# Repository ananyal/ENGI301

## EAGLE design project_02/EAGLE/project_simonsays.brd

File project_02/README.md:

Simon Says PCB
This repository provides the files for the PCB implementation of the following Hackster Project: https://www.hackster.io/al85/simon-says-pattern-mini-game-16e997

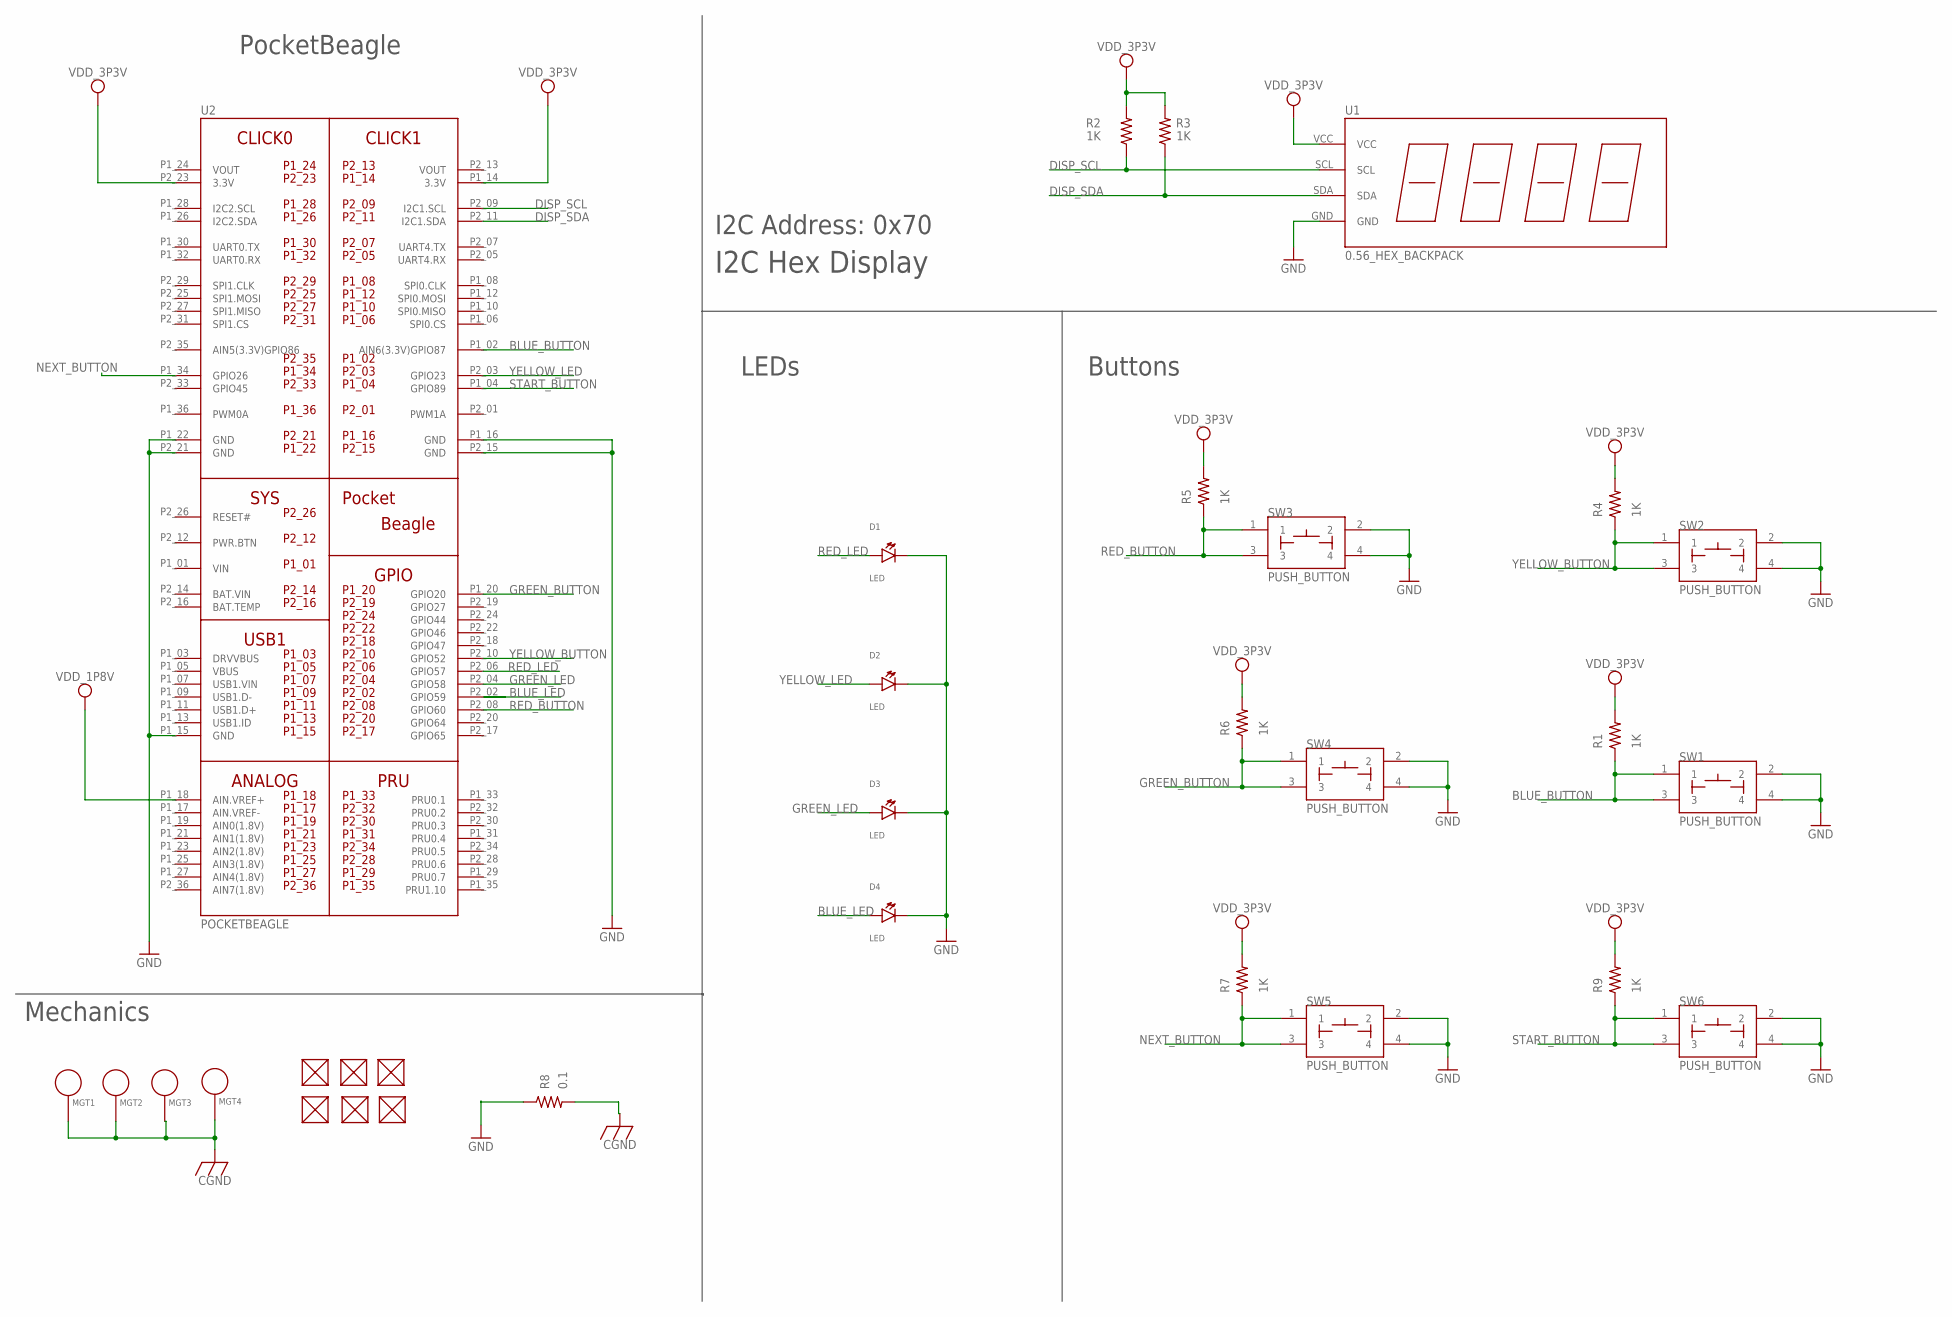
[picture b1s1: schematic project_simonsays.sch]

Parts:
D1, D2, D3, D4: LED; EIA-STD
FUD1, FUD2, FUD3, FUD4, FUD5, FUD6: FIDUCIAL; FIDUCIAL_40MIL
MGT1, MGT2, MGT3, MGT4: MOUNTING_HOLE
R1, R2, R3, R4, R5, R6, R7, R9: 1K; R0603
R8: 0.1; R0805
SW1, SW2, SW3, SW4, SW5, SW6: PUSH_BUTTON; BUTTON_12.5MM
U1: 0.56_HEX_BACKPACK
U2: POCKETBEAGLE

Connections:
BAT.VIN: U2.P2_14 (BAT.VIN)
BLUE_BUTTON: R1.1, SW1.1, SW1.3, U2.P1_02 (AIN6(3.3V)GPIO87)
BLUE_LED: D4.ANODE, U2.P2_02 (GPIO59)
CGND: MGT1.P$1, MGT2.P$1, MGT3.P$1, MGT4.P$1, R8.2
DISP_SCL: R2.1, U1.SCL, U2.P2_09 (I2C1.SCL)
DISP_SDA: R3.1, U1.SDA, U2.P2_11 (I2C1.SDA)
GND: D1.CATHODE, D2.CATHODE, D3.CATHODE, D4.CATHODE, R8.1, SW1.2, SW1.4, SW2.2, SW2.4, SW3.2, SW3.4, SW4.2, SW4.4, SW5.2, SW5.4, SW6.2, SW6.4, U1.GND, U2.P1_15 (GND), U2.P1_16 (GND), U2.P1_22 (GND), U2.P2_15 (GND), U2.P2_21 (GND)
GREEN_BUTTON: R6.1, SW4.1, SW4.3, U2.P1_20 (GPIO20)
GREEN_LED: D3.ANODE, U2.P2_04 (GPIO58)
NEXT_BUTTON: R7.1, SW5.1, SW5.3, U2.P1_34 (GPIO26)
RED_BUTTON: R5.1, SW3.1, SW3.3, U2.P2_08 (GPIO60)
RED_LED: D1.ANODE, U2.P2_06 (GPIO57)
START_BUTTON: R9.1, SW6.1, SW6.3, U2.P1_04 (GPIO89)
VDD_1P8V: U2.P1_18 (AIN.VREF+)
VDD_3P3V: R1.2, R2.2, R3.2, R4.2, R5.2, R6.2, R7.2, R9.2, U1.VCC, U2.P1_14 (3.3V), U2.P2_23 (3.3V)
VIN: U2.P1_01 (VIN)
VOUT: U2.P1_24 (VOUT), U2.P2_13 (VOUT)
YELLOW_BUTTON: R4.1, SW2.1, SW2.3, U2.P2_10 (GPIO52)
YELLOW_LED: D2.ANODE, U2.P2_03 (GPIO23)

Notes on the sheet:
I2C Hex Display
LEDs
Buttons
PocketBeagle
I2C Address: 0x70
Mechanics

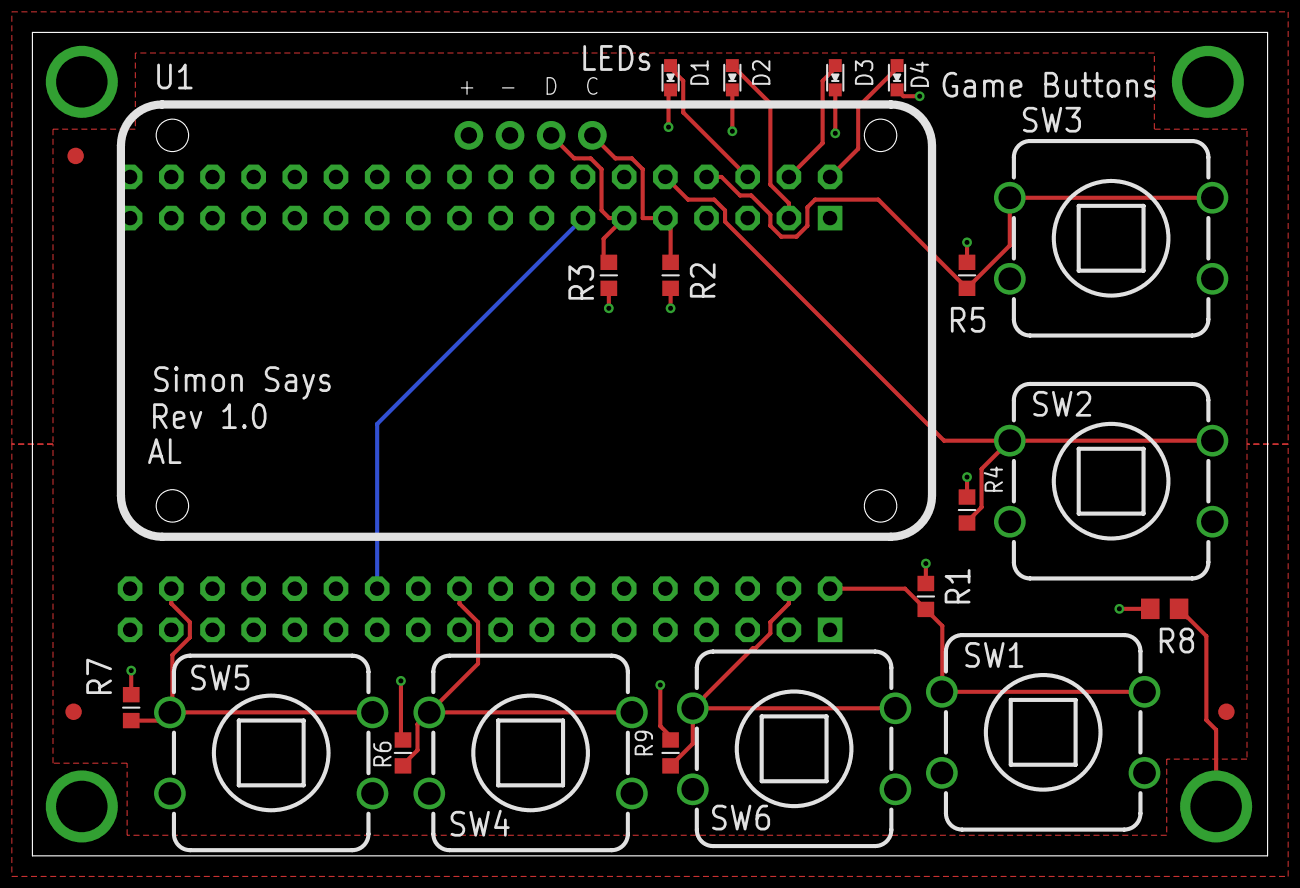
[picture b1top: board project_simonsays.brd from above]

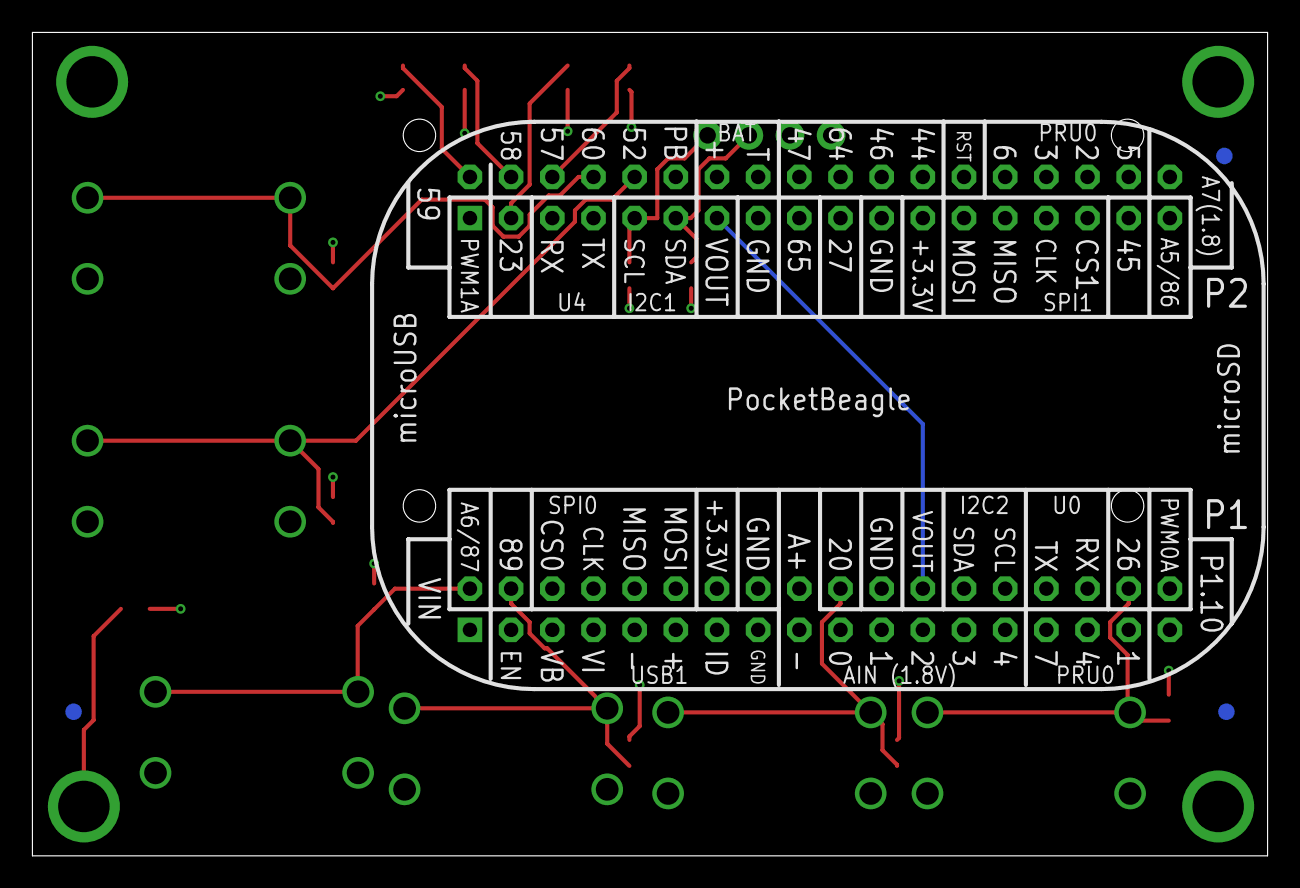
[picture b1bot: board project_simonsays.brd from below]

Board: 4 copper layers, 76.2 x 50.8 mm, 31 parts (4 on the bottom side), 16 nets.

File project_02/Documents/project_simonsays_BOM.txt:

Partlist exported from /Users/alingineni/Documents/EAGLE/projects/project_simonsays.sch at 12/15/23 5:07 PM

Qty Value             Device            Package           Parts                              Description                                    
1   0.1               R_R0805           R0805             R8                                 RESISTOR, American symbol                      
1   0.56_HEX_BACKPACK 0.56_HEX_BACKPACK 0.56_HEX_BACKPACK U1                                 0.56" LED HEX Backback - Adafruit HT16K33 -    
8   1K                R_R0603           R0603             R1, R2, R3, R4, R5, R6, R7, R9     RESISTOR, American symbol                      
6   FIDUCIAL          FIDUCIAL          FIDUCIAL_40MIL    FUD1, FUD2, FUD3, FUD4, FUD5, FUD6                                                
4   LED               LED               EIA-STD           D1, D2, D3, D4                     EIA-STD LED, LTST-C191TBKT                     
4   MOUNTING_HOLE     MOUNTING_HOLE     MOUNTING_HOLE     MGT1, MGT2, MGT3, MGT4             Chassis Mounting Hole w/GND connection ability 
1   POCKETBEAGLE      POCKETBEAGLE      POCKETBEAGLE      U2                                                                                
6   PUSH_BUTTON       PUSH_BUTTON       BUTTON_12.5MM     SW1, SW2, SW3, SW4, SW5, SW6

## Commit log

2023-09-27 Homework 4
2023-11-08 Add game to repository
2023-11-09 Committing Game
